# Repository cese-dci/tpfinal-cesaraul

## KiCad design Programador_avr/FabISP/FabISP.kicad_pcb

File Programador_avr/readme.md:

El FabISP es un programador para microcontroladores AVR, le permite programar los microcontroladores en otras placas que haga, utilizando nada más que un cable USB y un cable IDC de 6 pines a IDC de 6 pines. Se basa en los firmwares USBtiny y V-USB, que permiten al ATtiny44 realizar la comunicación USB en el software. La programación se puede realizar a través de avrdude. El esquema es : conector USB, ATtiny44 y encabezado ISP de 6 pines, con una variedad de componentes pasivos. Empecé con los archivos Eagle para USBtinyISP, aunque casi no queda nada. La mayoría de las piezas del FabISP se encuentran en (SparkFun, Digi-Key), el cristal de 12 MHz (Digi-Key) y los condensadores de 18 pF para el cristal (Digi-Key).

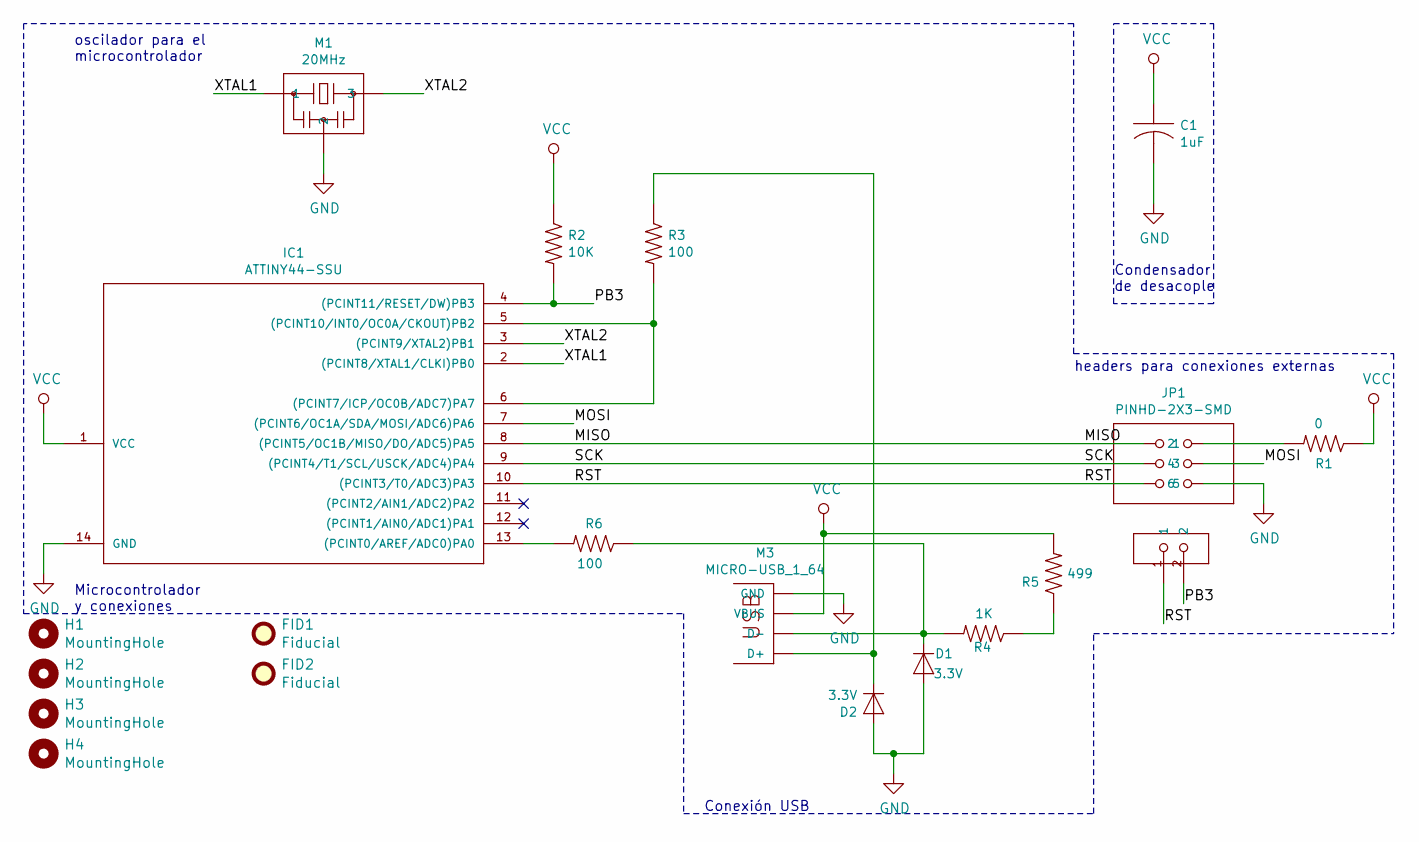
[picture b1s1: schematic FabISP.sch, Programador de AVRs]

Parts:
C1: 1uF; C_1206_3216Metric
D1, D2: 3.3V; fab-SOD123
FID1, FID2: Fiducial; Fiducial_1mm_Mask2mm
H1, H2, H3: MountingHole; MountingHole_2.1mm
H4: MountingHole; MountingHole_2.2mm_M2
IC1: ATTINY44-SSU; fab-SOIC-14_3.9x8.7mm_P1.27mm
JP1: PINHD-2X3-SMD; PinHeader_2x03_P1.00mm_Vertical_SMD
M1: 20MHz; fab-EFOBM
M2: PINHD-1x02-SMD-HEADER; PinHeader_2x01_P1.00mm_Vertical_SMD
M3: MICRO-USB_1_64; fab-DX4R005HJ5_64
R1: 0; R_1206_3216Metric
R2: 10K; R_1206_3216Metric
R3, R6: 100; R_1206_3216Metric
R4: 1K; R_1206_3216Metric
R5: 499; R_1206_3216Metric

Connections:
/MISO: IC1.8 ((PCINT5/OC1B/MISO/DO/ADC5)PA5), JP1.1
/MOSI: IC1.7 ((PCINT6/OC1A/SDA/MOSI/ADC6)PA6), JP1.4
/PB3: IC1.4 ((PCINT11/RESET/DW)PB3), M2.2, R2.2
/RST: IC1.10 ((PCINT3/T0/ADC3)PA3), JP1.5, M2.1
/SCK: IC1.9 ((PCINT4/T1/SCL/USCK/ADC4)PA4), JP1.3
/XTAL1: IC1.2 ((PCINT8/XTAL1/CLKI)PB0), M1.1
/XTAL2: IC1.3 ((PCINT9/XTAL2)PB1), M1.3
GND: C1.2, D1.ANODE (A), D2.ANODE (A), IC1.14 (GND), JP1.6, M1.2, M3.GND
unnamed: D1.CATHODE (C), M3.D-, R4.2, R6.1
unnamed: D2.CATHODE (C), M3.D+, R3.1
unnamed: IC1.5 ((PCINT10/INT0/OC0A/CKOUT)PB2), IC1.6 ((PCINT7/ICP/OC0B/ADC7)PA7), R3.2
unnamed: IC1.13 ((PCINT0/AREF/ADC0)PA0), R6.2
unnamed: JP1.2, R1.2
unnamed: R4.1, R5.1
VCC: C1.1, IC1.1 (VCC), M3.VBUS, R1.1, R2.1, R5.2

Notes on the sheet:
Conexión USB
headers para conexiones externas
Condensador de desacople
Microcontrolador y conexiones
oscilador para el microcontrolador

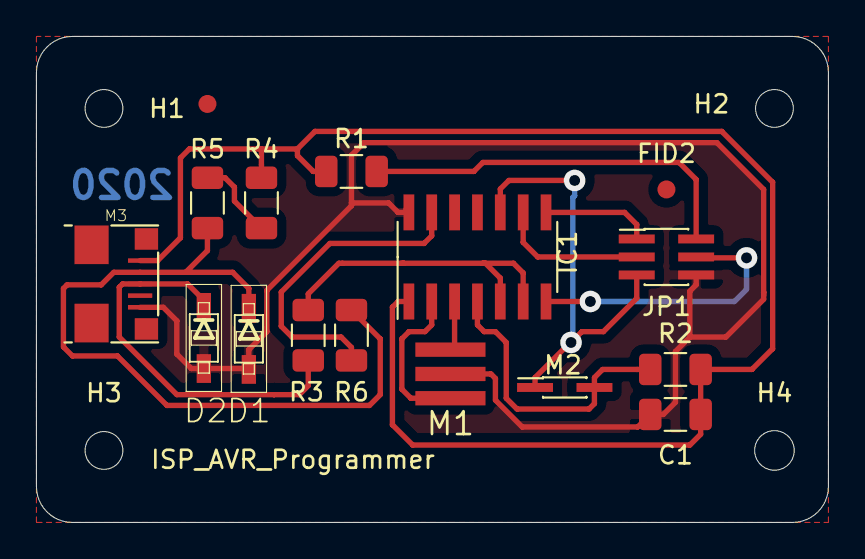
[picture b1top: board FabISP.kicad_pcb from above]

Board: 2 copper layers, 44.0 x 27.0 mm, 20 parts (1 on the bottom side), 15 nets.

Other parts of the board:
FIDe: Fiducial; Fiducial_1mm_Mask2mm

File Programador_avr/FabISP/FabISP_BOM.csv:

"Id";"Identificador";"Empaquetado";"Cantidad";"Identificación";"Suministrador y ref";
1;"D2,D1";"fab-SOD123";2;" ";;;
2;"IC1";"fab-SOIC-14_3.9x8.7mm_P1.27mm";1;"ATTINY44";;;
3;"M1";"fab-EFOBM";1;"Reson.";;;
4;"M3";"fab-DX4R005HJ5_64";1;"MICRO-USB";;;
5;"C1";"C_1206_3216Metric";1;"1uF";;;
6;"JP1";"PinHeader_2x03_P1.00mm_Vertical_SMD";1;"PINHD-2X3-SMD";;;
7;"M2,M4";"PinHeader_2x01_P1.00mm_Vertical_SMD";2;"PINHD-1x02-SMD-HEADER";;;
8;"R2";"R_1206_3216Metric";1;"10K";;;
9;"R3,R6";"R_1206_3216Metric";2;"100";;;
10;"R4";"R_1206_3216Metric";1;"1K";;;
11;"R5";"R_1206_3216Metric";1;"499";;;

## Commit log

2020-05-29 test y creación de archivos de proyecto
2020-06-09 potencia y acopladores
2020-09-25 creación de proyecto
2020-09-25 agregado componentes
2020-09-25 componentes completos
2020-10-16 Conexiones USB
2020-10-16 Conexiones completas queda Pendiente agregar etiquetas
2020-10-16 Circuito completo con huellas
2020-10-16 Posicionamiento de componentes
2020-10-21 corrección de huellas y primeras rutas de pcb
2020-11-03 pcb 90%
2020-11-03 PCB 100% pendiente para mejoras
2020-11-07 correcciones sch y pcb
2020-11-07 correcciones
2020-11-07 orgnización de serigrafía y correcciones DRC
2020-11-07 Generación de BOM y gerbers
2020-11-07 cambios y correcciones listas para revisión de compañero y docente
2020-11-07 mejora de vistas
2020-11-14 Documentación
2020-11-14 Documentación mas imagen de referencia
2020-11-14 Corrección SCH Se hicieron las conexiones reemplazando etiquetas se agrego información de componentes se agregó información solicitada
2020-11-14 Se corrigió todas las vías al tamaño sugerido, se mejoró la ubicación de componentes sugeridos, se realizaron cambios en las vías
2020-11-14 Se hicieron los cambios sugeridos de ubicación de componentes asi como aproximaciín de circuito integrado a usb
2020-11-15 se agrego componentes en 3D se corrigió nodo tierra y esquemático, se agregó agujero de sujeción
2020-11-15 acomodado de componentes
2020-11-15 actualización PCB
2020-11-18 comentatios DWgs, Corrección de margendes
2020-11-18 fiduciales y mejora de distribución
2020-11-18 Diseño para revisión

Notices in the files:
Programador_avr/FabISP/FabISP.sch:
MIT License
